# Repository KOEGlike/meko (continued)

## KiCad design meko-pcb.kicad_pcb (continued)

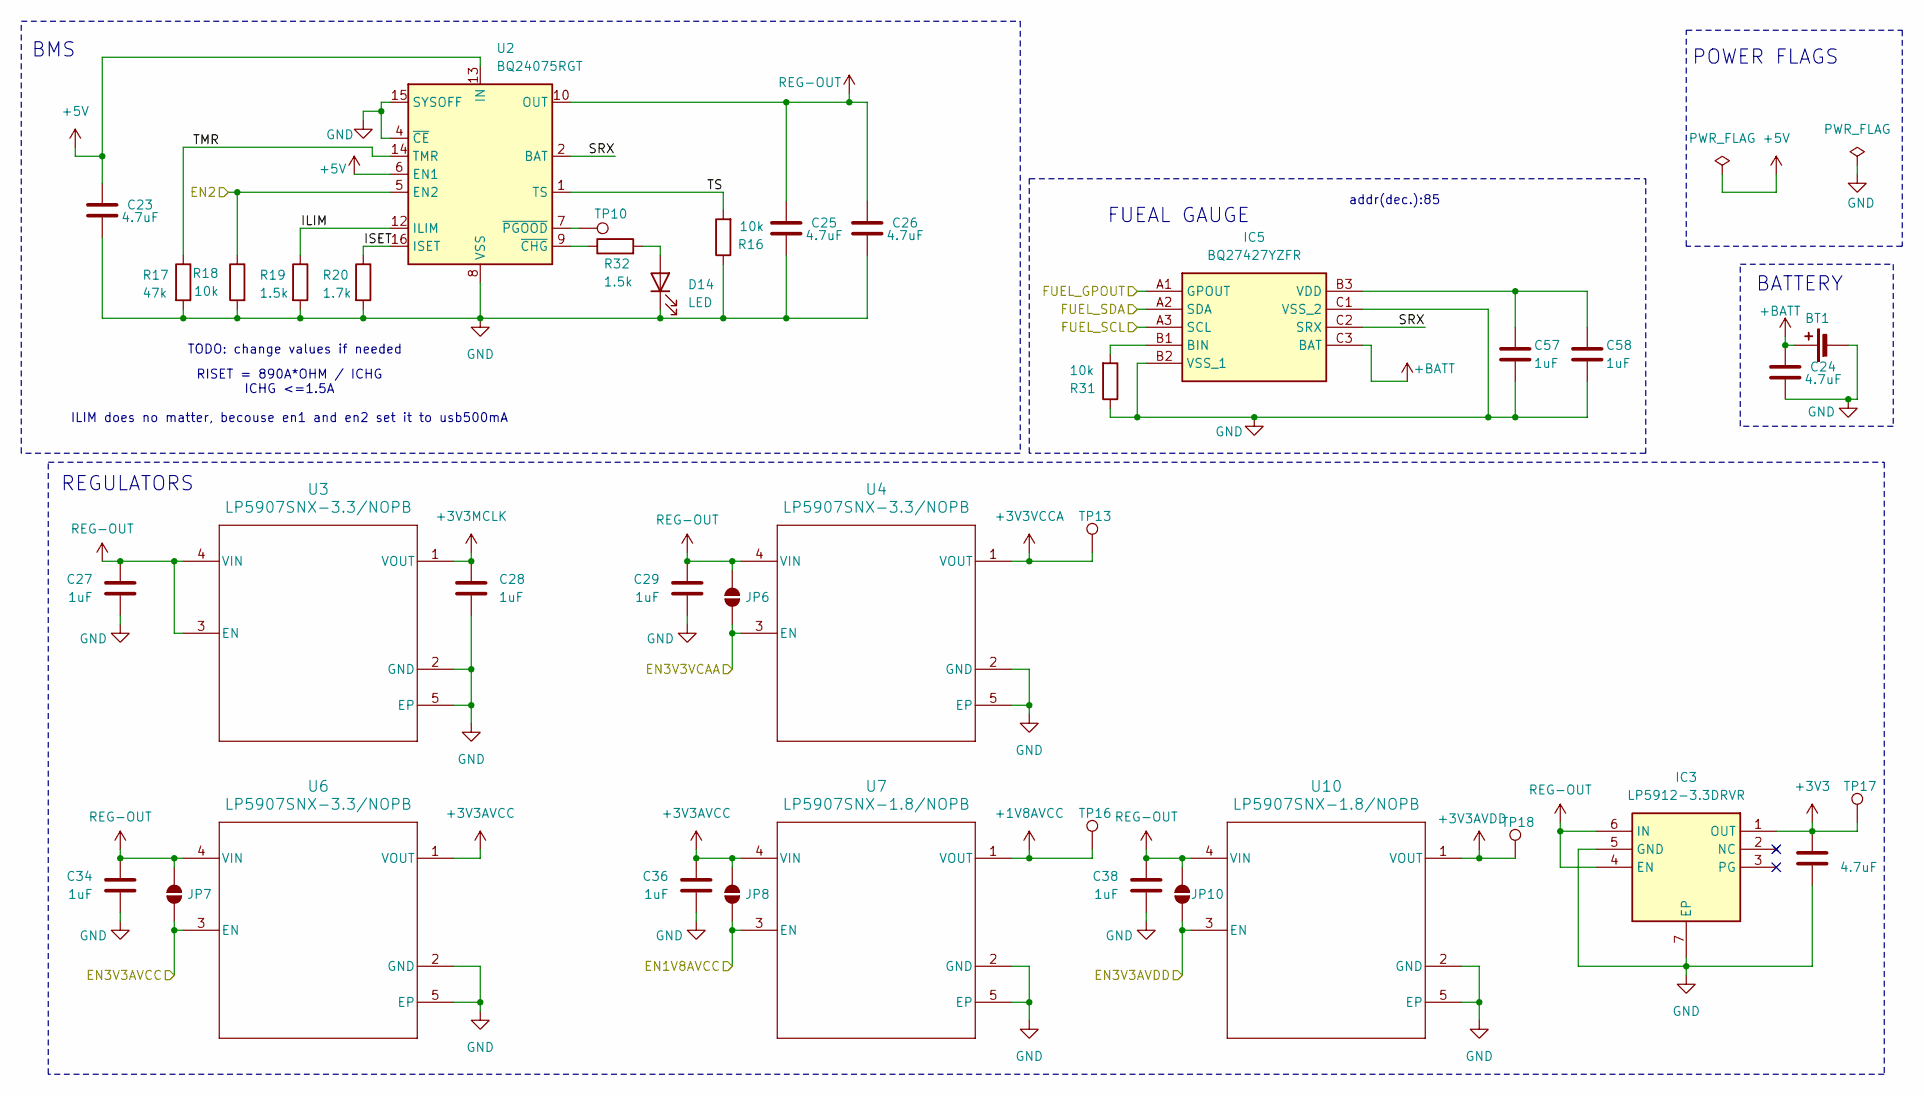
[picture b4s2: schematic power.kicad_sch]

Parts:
BT1: Battery_Cell; JST_S2B-PH-SM4-TB_LF__SN_
C23, C24, C25, C26: 4.7uF; C_0402_1005Metric; LCSC C307423
C27, C28, C29, C34, C36, C38, C57, C58: 1uF; C_0402_1005Metric
C33: 4.7uF; C_0402_1005Metric
D14: LED; LED_0603_1608Metric
IC3: LP5912-3.3DRVR; SON65P200X200X80-7N; Manufacturer_Part_Number LP5912-3.3DRVR; Mouser Part Number 595-LP5912-3.3DRVR
IC5: BQ27427YZFR; BGA9C50P3X3_158X162X62; Manufacturer_Part_Number BQ27427YZFR; Mouser Part Number 595-BQ27427YZFR
JP6, JP7, JP8, JP10: SolderJumper_2_Open; SolderJumper-2_P1.3mm_Open_RoundedPad1.0x1.5mm
R16, R31: 10k; R_0402_1005Metric; LCSC C25744
R17: 47k; R_0402_1005Metric; LCSC C93943
R18: 10k; R_0402_1005Metric
R19: 1.5k; R_0402_1005Metric; LCSC C25867
R20: 1.7k; R_0402_1005Metric; LCSC C131467
R32: 1.5k; R_0402_1005Metric; LCSC C25744
TP10, TP13, TP16, TP17, TP18: TestPoint; TestPoint_Pad_D1.0mm
U2: BQ24075RGT; VQFN-16-1EP_3x3mm_P0.5mm_EP1.6x1.6mm
U3, U4, U6: LP5907SNX-3.3/NOPB; Texas_X2SON-4_1x1mm_P0.65mm
U7, U10: LP5907SNX-1.8/NOPB; Texas_X2SON-4_1x1mm_P0.65mm

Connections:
+1V8AVCC: TP16.1, U7.1 (VOUT); also elsewhere on the board
+3V3: C33.1, IC3.1 (OUT), TP17.1; also elsewhere on the board
+3V3AVCC: C36.1, JP8.1 (A), U6.1 (VOUT), U7.4 (VIN); also elsewhere on the board
+3V3AVDD: TP18.1, U10.1 (VOUT); also elsewhere on the board
+3V3MCLK: C28.1, U3.1 (VOUT); also elsewhere on the board
+3V3VCCA: TP13.1, U4.1 (VOUT); also elsewhere on the board
+5V: C23.2, U2.6 (EN1), U2.13 (IN); also elsewhere on the board
+BATT: BT1.1 (+), C24.2, IC5.C3 (BAT)
/I2C_SCL: IC5.A3 (SCL); also elsewhere on the board
/I2C_SDA: IC5.A2 (SDA); also elsewhere on the board
/PWR_EN1V8AVCC: JP8.2 (B), U7.3 (EN); also elsewhere on the board
/PWR_EN3V3AVCC: JP7.2 (B), U6.3 (EN); also elsewhere on the board
/PWR_EN3V3AVDD: JP10.2 (B), U10.3 (EN); also elsewhere on the board
/PWR_EN3V3VCCA: JP6.2 (B), U4.3 (EN); also elsewhere on the board
/PWR_EN_USB: R18.1, U2.5 (EN2); also elsewhere on the board
/PWR_FUEL_GPOUT: IC5.A1 (GPOUT); also elsewhere on the board
/power/ILIM: R19.1, U2.12 (ILIM)
/power/ISET: R20.1, U2.16 (ISET)
/power/SRX: IC5.C2 (SRX), U2.2 (BAT), U2.3 (BAT)
/power/TMR: R17.1, U2.14 (TMR)
/power/TS: R16.2, U2.1 (TS)
GND: BT1.2 (-), C23.1, C24.1, C25.1, C26.1, C27.2, C28.2, C29.2, C33.2, C34.2, C36.2, C38.2, C57.2, C58.2, D14.1 (K), IC3.5 (GND), IC3.7 (EP), IC5.B2 (VSS_1), IC5.C1 (VSS_2), R16.1, R17.2, R18.2, R19.2, R20.2, R31.1, U2.4 (~CE), U2.8 (VSS), U2.15 (SYSOFF), U2.17 (VSS), U3.2 (GND), U3.5 (EP), U4.2 (GND), U4.5 (EP), U6.2 (GND), U6.5 (EP), U7.2 (GND), U7.5 (EP), U10.2 (GND), U10.5 (EP); also elsewhere on the board
unnamed: D14.2 (A), R32.2
unnamed: IC5.B1 (BIN), R31.2
unnamed: C57.1, C58.1, IC5.B3 (VDD)
unnamed: R32.1, U2.9 (~CHG)
unnamed: TP10.1, U2.7 (~PGOOD)
REG-OUT: C25.2, C26.2, C27.1, C29.1, C34.1, C38.1, IC3.4 (EN), IC3.6 (IN), JP6.1 (A), JP7.1 (A), JP10.1 (A), U2.10 (OUT), U2.11 (OUT), U3.3 (EN), U3.4 (VIN), U4.4 (VIN), U6.4 (VIN), U10.4 (VIN)

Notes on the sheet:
TODO: change values if needed
FUEAL GAUGE
BMS
POWER FLAGS
RISET = 890A*OHM / ICHG ICHG <=1.5A ILIM does no matter, becouse en1 and en2 set it to usb500mA
BATTERY
addr(dec.):85
REGULATORS

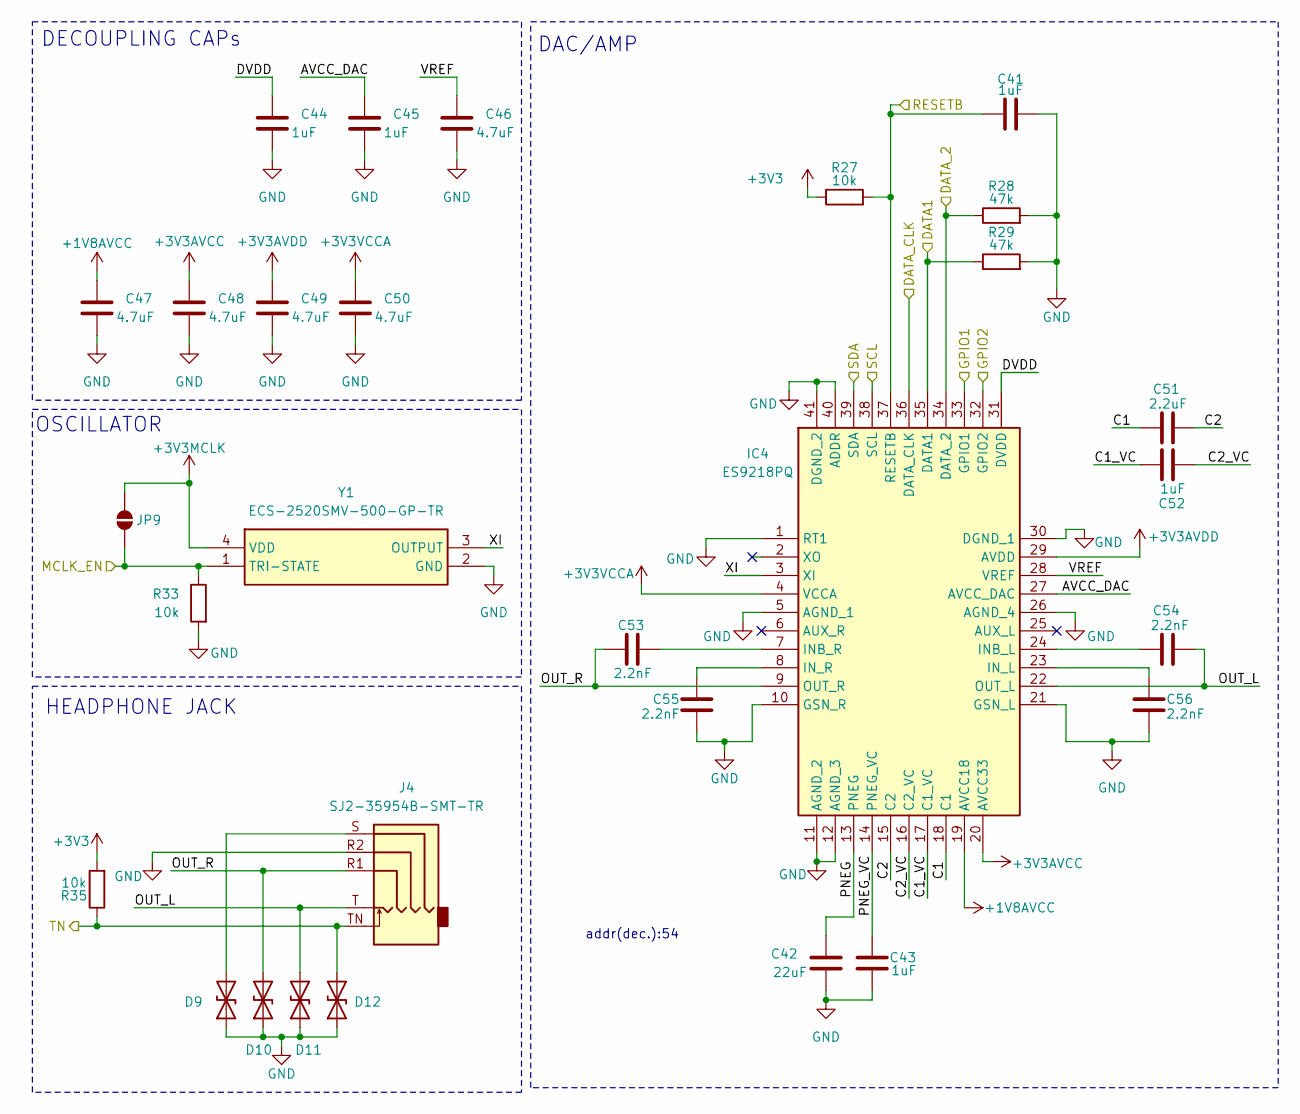
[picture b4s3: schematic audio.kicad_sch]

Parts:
C41, C43, C44, C45, C52: 1uF; C_0402_1005Metric
C42: 22uF; C_0603_1608Metric
C46, C47, C48, C49, C50: 4.7uF; C_0402_1005Metric
C51: 2.2uF; C_0402_1005Metric
C53, C54, C55, C56: 2.2nF; C_0402_1005Metric
D9, D10, D11, D12: D_TVS; CD0201T20LC
IC4: ES9218PQ; QFN40P500X500X80-41N-D; Manufacturer_Part_Number ES9218PQ; Mouser Part Number 460-ES9218PQ
J4: SJ2-35954B-SMT-TR; CUI_SJ2-35954B-SMT-TR
JP9: SolderJumper_2_Open; SolderJumper-2_P1.3mm_Open_RoundedPad1.0x1.5mm
R27, R33, R35: 10k; R_0402_1005Metric
R28, R29: 47k; R_0402_1005Metric
Y1: ECS-2520SMV-500-GP-TR; ECS2520SMV500GPTR; Manufacturer_Part_Number ECS-2520SMV-500-GP-TR; Mouser Part Number 520-2520SMV-500-GP-T

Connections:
+1V8AVCC: C47.1, IC4.19 (AVCC18); also elsewhere on the board
+3V3: R27.1, R35.2; also elsewhere on the board
+3V3AVCC: C48.1, IC4.20 (AVCC33); also elsewhere on the board
+3V3AVDD: C49.1, IC4.29 (AVDD); also elsewhere on the board
+3V3MCLK: JP9.1 (A), Y1.4 (VDD); also elsewhere on the board
+3V3VCCA: C50.1, IC4.4 (VCCA); also elsewhere on the board
/AUDIO_DATA1: IC4.35 (DATA1), R29.1; also elsewhere on the board
/AUDIO_DATA_2: IC4.34 (DATA_2), R28.1; also elsewhere on the board
/AUDIO_DATA_CLK/BOOT: IC4.36 (DATA_CLK); also elsewhere on the board
/AUDIO_DISPL_RESETB: C41.2, IC4.37 (RESETB), R27.2; also elsewhere on the board
/AUDIO_MLCK_EN: JP9.2 (B), R33.1, Y1.1 (TRI-STATE); also elsewhere on the board
/AUDIO_TN: D12.2 (A2), J4.TN, R35.1; also elsewhere on the board
/I2C_SCL: IC4.38 (SCL); also elsewhere on the board
/I2C_SDA: IC4.39 (SDA); also elsewhere on the board
/audio/AVCC_DAC: C45.1, IC4.27 (AVCC_DAC)
/audio/C1: C51.1, IC4.18 (C1)
/audio/C1_VC: C52.1, IC4.17 (C1_VC)
/audio/C2: C51.2, IC4.15 (C2)
/audio/C2_VC: C52.2, IC4.16 (C2_VC)
/audio/DVDD: C44.1, IC4.31 (DVDD)
/audio/GPIO1: IC4.33 (GPIO1)
/audio/GPIO2: IC4.32 (GPIO2)
/audio/OUT_L: C54.2, D11.2 (A2), IC4.22 (OUT_L), J4.T
/audio/OUT_R: C53.1, D10.2 (A2), IC4.9 (OUT_R), J4.R1
/audio/PNEG: C42.1, IC4.13 (PNEG)
/audio/PNEG_VC: C43.1, IC4.14 (PNEG_VC)
/audio/VREF: C46.1, IC4.28 (VREF)
/audio/XI: IC4.3 (XI), Y1.3 (OUTPUT)
GND: C41.1, C42.2, C43.2, C44.2, C45.2, C46.2, C47.2, C48.2, C49.2, C50.2, C55.1, C56.1, D9.1 (A1), D10.1 (A1), D11.1 (A1), D12.1 (A1), IC4.1 (RT1), IC4.5 (AGND_1), IC4.10 (GSN_R), IC4.11 (AGND_2), IC4.12 (AGND_3), IC4.21 (GSN_L), IC4.26 (AGND_4), IC4.30 (DGND_1), IC4.40 (ADDR), IC4.41 (DGND_2), J4.R2, R28.2, R29.2, R33.2, Y1.2 (GND); also elsewhere on the board
unnamed: D9.2 (A2), J4.S
unnamed: C54.1, IC4.24 (INB_L)
unnamed: C53.2, IC4.7 (INB_R)
unnamed: C56.2, IC4.23 (IN_L)
unnamed: C55.2, IC4.8 (IN_R)

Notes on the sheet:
DAC/AMP
OSCILLATOR
addr(dec.):54
HEADPHONE JACK
DECOUPLING CAPs

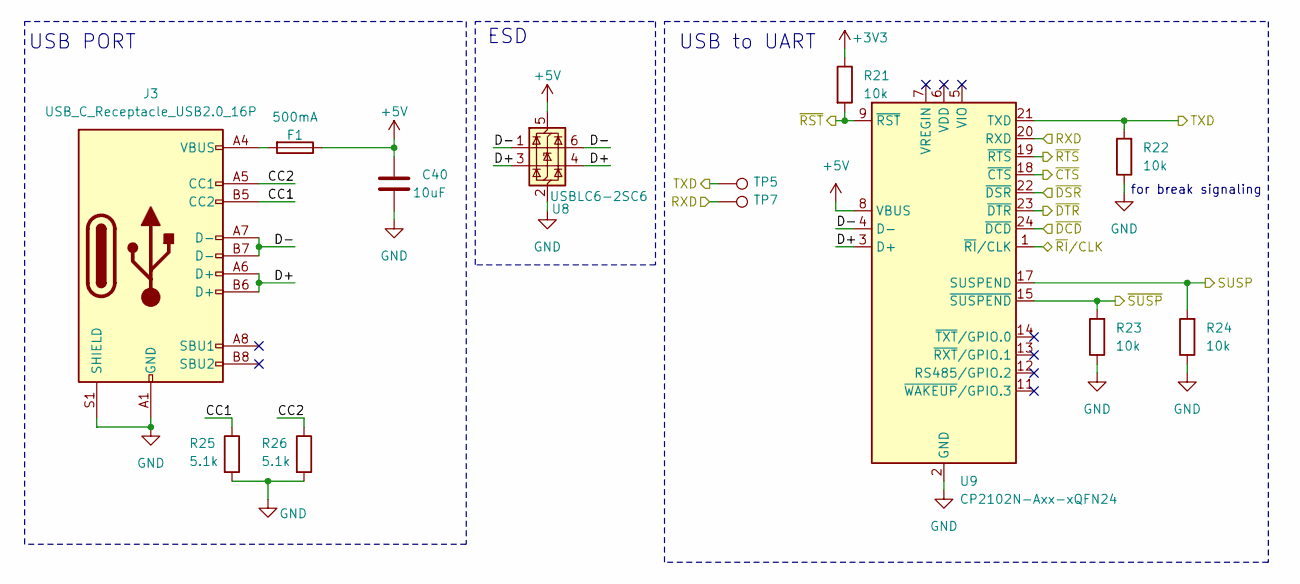
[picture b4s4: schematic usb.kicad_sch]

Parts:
C40: 10uF; C_0402_1005Metric
F1: 500mA; Fuse_0603_1608Metric; LCSC C210357
J3: USB_C_Receptacle_USB2.0_16P; USB_C_Receptacle_GCT_USB4105-xx-A_16P_TopMnt_Horizontal
R21, R22, R23, R24: 10k; R_0402_1005Metric
R25, R26: 5.1k; R_0402_1005Metric; LCSC C25905
TP5, TP7: TestPoint; TestPoint_Pad_D1.0mm
U8: USBLC6-2SC6; SOT-23-6; LCSC C7519
U9: CP2102N-Axx-xQFN24; QFN-24-1EP_4x4mm_P0.5mm_EP2.6x2.6mm

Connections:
+3V3: R21.1; also elsewhere on the board
+5V: C40.1, F1.1, U8.5 (VBUS), U9.8 (VBUS); also elsewhere on the board
/PWR_EN_USB: R24.2, U9.17 (SUSPEND); also elsewhere on the board
/RXD: R22.2, TP5.1, U9.21 (TXD); also elsewhere on the board
/TXD: TP7.1, U9.20 (RXD); also elsewhere on the board
/USB/CC1: J3.B5 (CC2), R25.1
/USB/CC2: J3.A5 (CC1), R26.1
/USB/D+: J3.A6 (D+), J3.B6 (D+), U8.3 (I/O2), U8.4 (I/O2), U9.3 (D+)
/USB/D-: J3.A7 (D-), J3.B7 (D-), U8.1 (I/O1), U8.6 (I/O1), U9.4 (D-)
/USB/~CTS: U9.18 (~CTS); also elsewhere on the board
/USB/~DCD: U9.24 (~DCD); also elsewhere on the board
/USB/~DSR: U9.22 (~DSR); also elsewhere on the board
/USB/~RI/CLK: U9.1 (~RI/CLK); also elsewhere on the board
/USB/~RTS: U9.19 (~RTS)
/USB/~SUSP: R23.2, U9.15 (~SUSPEND); also elsewhere on the board
/~DTR: U9.23 (~DTR); also elsewhere on the board
/~RST: R21.2, U9.9 (~RST); also elsewhere on the board
GND: C40.2, J3.A1 (GND), J3.A12 (GND), J3.B1 (GND), J3.B12 (GND), J3.S1 (SHIELD), R22.1, R23.1, R24.1, R25.2, R26.2, U8.2 (GND), U9.2 (GND), U9.25 (GND); also elsewhere on the board
unnamed: F1.2, J3.A4 (VBUS), J3.A9 (VBUS), J3.B4 (VBUS), J3.B9 (VBUS)

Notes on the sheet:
USB PORT
ESD
for break signaling
USB to UART

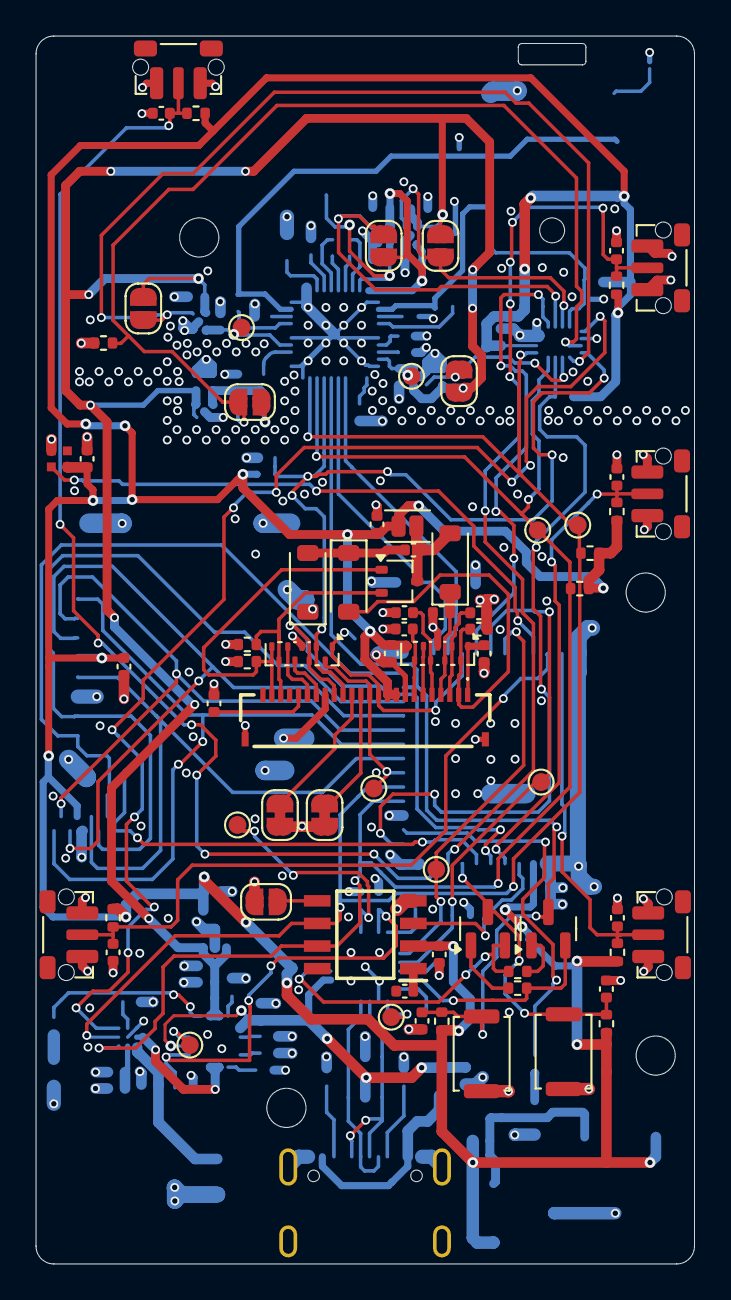
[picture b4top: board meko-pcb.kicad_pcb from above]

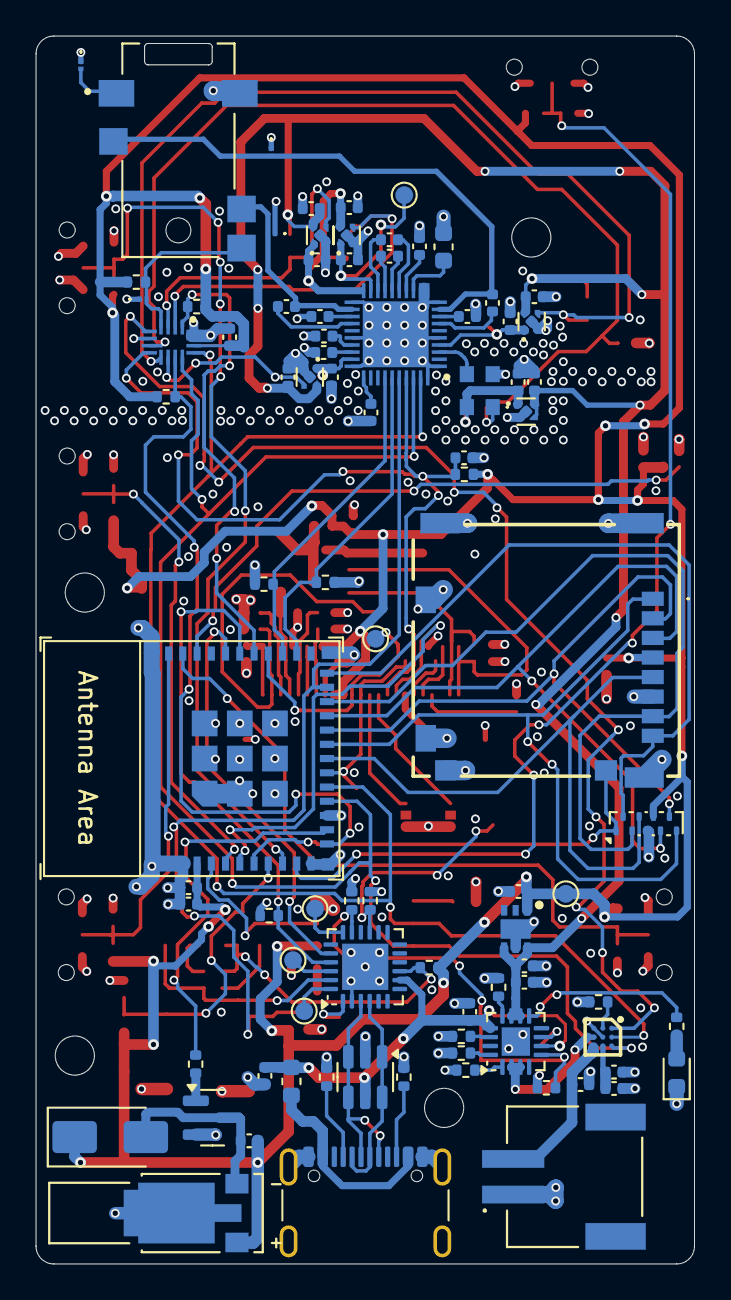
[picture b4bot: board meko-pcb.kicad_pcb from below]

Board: 4 copper layers, 37.0 x 69.0 mm, 164 parts (88 on the bottom side), 108 nets.

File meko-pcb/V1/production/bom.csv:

Designator,Footprint,Quantity,Value,LCSC Part #
BT1,JST_S2B-PH-SM4-TB_LF__SN_,1,Battery_Cell,
"C1, C2, C3, C30, C4, C5, C6, C61, C7, C8",0402,10,100nF,
"C10, C11, C12, C13, C14, C15, C16, C17, C18, C19, C20, C21, C22, C27, C28, C29, C34, C36, C38, C41, C43, C44, C45, C52, C57, C58, C9",0402,27,1uF,
"C23, C24, C25, C26, C60",0402,5,4.7uF,C307423
"C33, C46, C47, C48, C49, C50",0402,6,4.7uF,
C40,0402,1,10uF,
C42,0603,1,22uF,
C51,0402,1,2.2uF,
"C53, C54, C55, C56",0402,4,2.2nF,
D1,D_SMA,1,US1B,
"D10, D11, D12, D9",CD0201T20LC,4,D_TVS,
D14,0603,1,LED,
D2,sk6805ec14,1,SK6805,
"D3, D4, D5",D_SOD-123,3,MBR0530,
"D6, D7, D8",Diodes_UDFN3810-9_TYPE_B-better-pinout,3,D3V3X8U9LP3810,
F1,0603,1,500mA,C210357
IC1,SOIC127P600X175-8N,1,AS5600-ASOM,
IC2,QFN40P180X260X55-16N,1,TCAL9538RSVR,
IC3,SON65P200X200X80-7N,1,LP5912-3.3DRVR,
IC4,QFN40P500X500X80-41N-D,1,ES9218PQ,
IC5,BGA9C50P3X3_158X162X62,1,BQ27427YZFR,
J1,FH34SRJ24S05SH99-disp,1,GDEY0154D67,
J2,MEM20900014500A,1,MEM2090-00-145-00-A,
J3,USB_C_Receptacle_GCT_USB4105-xx-A_16P_TopMnt_Horizontal,1,USB_C_Receptacle_USB2.0_16P,
J4,CUI_SJ2-35954B-SMT-TR,1,SJ2-35954B-SMT-TR,
L1,L_TDK_MLZ2012_h1.25mm,1,47uF,
M1,PUI_HD-EMB1204-SM,1,HD-EMB1204-SM,
"Q1, Q2, Q3",SOT-23,3,SS8050,
Q4,SOT-323_SC-70,1,Si1308EDL,
"R1, R10, R11, R14, R15, R18, R2, R21, R22, R23, R24, R27, R3, R33, R35, R4, R5, R6, R7, R8",0402,20,10k,
R12,0402,1,1M,
R13,0402,1,2.2R,
"R16, R31",0402,2,10k,C25744
R17,0402,1,47k, C93943
R19,0402,1,1.5k,C25867
R20,0402,1,1.7k,C131467
"R25, R26",0402,2,5.1k,C25905
"R28, R29",0402,2,47k,
R30,0402,1,100k,
R32,0402,1,1.5k,C25744
R9,0402,1,1k,
"SW1, SW2, SW3, SW4, SW5",SW_Push_1P1T-MP_NO_Horizontal_Alps_SKRTLAE010,5,SW_Push,
"SW6, SW7",SW_Push_SPST_NO_Alps_SKRK,2,SW_Push,
"TP1, TP10, TP13, TP16, TP17, TP18, TP19, TP2, TP20, TP21, TP22, TP3, TP4, TP5, TP6, TP7",TestPoint_Pad_D1.0mm,16,TestPoint,
U1,ESP32-PICO-MINI-02,1,ESP32-PICO-MINI-02,
"U10, U7",Texas_X2SON-4_1x1mm_P0.65mm,2,LP5907SNX-1.8/NOPB,
U2,VQFN-16-1EP_3x3mm_P0.5mm_EP1.6x1.6mm,1,BQ24075RGT,
"U3, U4, U6",Texas_X2SON-4_1x1mm_P0.65mm,3,LP5907SNX-3.3/NOPB,
U8,SOT-23-6,1,USBLC6-2SC6,C7519
U9,QFN-24-1EP_4x4mm_P0.5mm_EP2.6x2.6mm,1,CP2102N-Axx-xQFN24,
Y1,ECS2520SMV500GPTR,1,ECS-2520SMV-500-GP-TR,

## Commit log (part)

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2025-06-21 added renders, other small stuff
2025-06-21 added WHY section to readme
2025-06-21 jouranl update
2025-06-22 added images
2025-06-22 scaled images
2025-06-25 Update README.md
    added link to firmware repo
2025-06-29 new blender scene
2025-08-09 added firmware submodule
2025-08-09 Update submodule path in .gitmodules to 'firmware'
2025-08-09 fixed typeo in readme
2025-10-04 Implement code changes to enhance functionality and improve performance
2025-10-04 changed image
2025-10-12 started to implement nrf53
2025-10-14 continued work om nrf53
2025-10-16 started to implement npm1300
2025-10-19 added new ldos, made improvements to the schematic
2025-10-20 moved everything to one sheet, finished rough schematic
    finished power train, made the modules of the schematic more interconnected with tracs, removed unneded nets, seperated nets, connected everythin to the soc
2025-10-21 many small fixes
2025-10-21 renamed oscillator to crystal
2025-10-25 switched from the ESS dac to a TI dac
    the preformance is better/same, its easier to implement, cheaper, in stock at lcsc
2025-10-26 swithced out dacs
2025-10-27 added final touches
2025-10-27 Smalll updatesd
2025-10-28 small chnages
2025-10-28 added a bumch of testpoints/jumpers, fixed dac i2c adress pin
2025-10-29 changed parts that are not avalibile on lcsc
2025-10-29 fixed edge cuts
2025-11-02 started layout
2025-11-05 almost finished with general layout
    this will most certanily evolve
2025-11-06 finished first pass of rough layout
    i still need to add 3d modles
2025-11-06 moved some stuff around
2025-11-12 removed caps from software controlled buttons, placed jumpers
2025-11-13 made schematic prettier
2025-11-14 routed some traces
2025-11-15 routed a bunch of traces
2025-11-15 routed more traces
2025-11-15 re did the layout of the dac
2025-11-15 forgor to save
2025-11-15 moved pin assignments for better layout, redid analog layout
2025-11-16 rf, routed stuff
2025-11-17 messed around with gound fill
2025-11-18 almost finished
    routed all traces, still need to place testpoints
2025-11-19 places all the testpoints
2025-11-20 added 3d models, moved vibration motor around
2025-11-20 moved a cap
2025-11-20 made final changes
2025-11-20 filled zone
2025-11-22 fixed mistake in asom
2025-11-22 re calculated usb impedance, switched reference plane for the antenna
2025-11-22 added a 3d model
2025-11-22 updated component placement to match the previous design, updated case
2025-11-22 made visible some stuff in cad
2025-11-23 assigned all the mpns and lcsc numbers
2025-11-23 updated bom and readme
2025-11-23 fixed csv
2025-11-23 removed unneeded stuff
2025-11-23 removed old renders
2025-11-23 updated components
2025-11-23 exported step
2025-11-23 updated bom
2025-11-27 optimzed bom
2025-11-27 made load caps dnp, cuz the nrf has internal ones
2025-11-27 updated a cap
2025-11-27 fixed motor and resistor interference
2025-11-28 updated motor foorprint, added 3d moedel
2025-11-29 chose a new crystal, so i can remove all 4 load caps
2025-11-29 made new renders
2025-11-29 updated readme with new renders
2025-11-29 made a new render
2025-11-29 updated front image in README.md
2025-12-01 added back v1 journal
2026-03-03 Remodelled the case in fusion
2026-03-03 Configure firmware submodule to track main branch
2026-03-14 Update README with firmware changes and remove parameters
    Removed detailed parameters section for 3D printing and updated firmware information.
2026-03-14 updated journal with all entries
2026-03-14 Rename V1_JOURNAL.md to JOURNAL_V1.md
2026-03-14 Change image links to new CDN format
    Updated image links to use a new CDN for better accessibility.
2026-03-17 Create Ll
2026-03-17 Add images to README for better presentation
    Added images to enhance the visual appeal of the README.
